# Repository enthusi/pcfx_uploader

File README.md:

# PCFX Uploader
transmitting data from PC to a NEC PC-FX via microcontroller in GPL v3 licence.

## Build
*microcontroller_code* contains the firmware in assembly for the LonganNano.\
*RP2040_device* contains information on how to build an alternate microcontroller board, and firmware (C & PIO Assembly) for this board.\
*pc_code* with the python script to upload data via UART connection.\
*pcfx_code* contains the client on NEC PC-FX side in v810 assembly (`make cd` will build an CD bin/cue image).

To build just type ```make``` in the corresponding folder, or launch the script, given that you have the following tools in your path:\
[RV32 Assembler Bronzebeard](https://github.com/theandrew168/bronzebeard)\
[v810 binutils](https://github.com/jbrandwood/v810-gcc)\
[pcfx-tools](https://github.com/jbrandwood/pcfxtools)

The RP2040 device is based on pico-sdk version 1.4.0.  To build, execute the command within 'build_xiao.sh', then 'cd build', and 'make'\
[pico-sdk](https://github.com/raspberrypi/pico-sdk)

## Summary
- the code on the PCFX side expects a magic word, start-address, execution-address and data length
- the code on the microcontroller mimics a PC-FX controller and sends all 32 keypad bits in the PC-FX specific protocol
- the code on the PC side simply connects to the microcontroller via UART
- The overall transmission speed is close to the UART limit despite a couple of extended wait loops on the PC-FX side. That could be optimized for speed if one really wanted to.

## Setup

### Longan Nano
This setup was used for initial development. The RP2040-based board will become the main supported plattform.\
The Longan Nano is hooked up to Port2 of the PC-FX via 3V-5V level shifts (though it _should_ be 5V tolerant)\
It uses 5 lines: GND, VCC, CLOCK, LATCH and DATA.\
The PC-FX pulls the LATCH line to low (0 Volts) when it wants more data to come in.
Then it sends a quick clock signal HIGH,LOW,HIGH,...\
The microcontroller senses that LATCH line, if it gets low, waits for it to get high then senses the CLOCK line and makes sure to put the proper
signal on the output DATA depending on the state of your data bit (0 or 1). Initially, I tested that in C on the raspberry PI with _some_ success.
But it became clear that it would be too instable. Then I went for a microcontroller (with only ~100 Mhz) in C. That worked but I wasn't totally happy.
Then I recoded the microcontroller in plain assembly (32bit RiscV, not too different from the PC-FX's native v810 CPU btw).
The PC connects via UART to the native UART lines of the Longan Nano.

### RP2040-based board
This operates the same as the Longan Nano, except observes the /OE line, which was found to control the direction of data on the DATA line (which
means that data can flow both *to* and *from* the PC-FX).
When this signal is high, the PC-FX sends data, so the microcontroller's output data line is tri-stated, and the signal is routed to an
alternate pin to be used for inbound data.
PIO assembly language is used for signal switching at high speeds, as this is its strength; the 'C' code merely acts as a traffic manager
for the data.
On this board, the USB port is used a virtual COM port, in order to keep the parts count to a minimum.

## Demonstration
YouTube recording of initial LonganNano variant:\

## Credits
- PC-FX code and Longan board design and code: *Martin 'enthusi' Wendt* [PriorArt](https://priorartgames.eu)
- RP2040 board design and code: *David Shadoff*

the folder *pc_code* contains the PC-FX binary `mandelbrot` from
[PC-FX Mandelbrot](https://github.com/enthusi/pcfx_fractal) which you can use to send as an example `python pysend.py mandelbrot`.\
See also: [PriorArt website](https://priorartgames.eu/2022/10/03/demo-mandelbrot-for-nec-pc-fx/)

## Research
[David Shadoff](https://github.com/dshadoff) tested the signals from '[test data line release'](https://github.com/enthusi/pcfx_uploader/releases/tag/testing_output) based on a RP2040 setup with his logic analyzer and confirms our expectation, that the data line is indeed bidirectional. Also the OE signal change flags the used direction.\

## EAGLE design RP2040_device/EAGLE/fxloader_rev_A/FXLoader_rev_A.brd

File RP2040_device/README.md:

# PCFX Uploader RP2040 Device

## Overview

This section of the repository includes PC Board designs and instructions for building a PC-FX communications device, and
also includes the firware in order to work in concert with the PC-FX and PC components elsewhere in this repository.

## PC Boards and Assembly

I designed all boards using the free version of EAGLE (2-layer, less than 100mm on both X- and Y- axes).
The gerbers are included in this repository, in case you want to get your own set made.

I have included the gerbers and relevant bom.csv and assembly.csv files to get these boards
assembled by JLCPCB, but you will still need the following parts:
- (1) Seeed Studio XIAO RP2040 microcontroller board
- (1) 6-pin right-angle through-hole pin header with 0.1" spacing.
- (7) Mill-Max Manufacturing part number 4401-0-15-80-18-27-04-0 "Receptacle with a standard tail" for creating a custom controller connector.
These are available at Digi-Key/Mouser.

You may also want to use male/female pin header sockets in case you need to remove the microcontroller board.
I recommend using short/low-profile header sockets in this case.

... These boards are solderable along the castellation, which is the recommended approach for assembly.

### Steps to assembly - Connector Board

Soldering the connector has a slightly more complicated process than the microcontroller board.  It's best not to have the pins penetrate all
the way through the board.  This is how I do it:
1. Insert the 7 Mill-Max connector pins into the PC-FX connector; you can use a pair of needle-nose pliers to assist in positioning.
2. Make sure to have one or two strands of speaker wire between the rows of pins; these will be used to extract the connector when
soldering is complete, but this wire should not be soldered to any part of the connector.
3. Position the connector board on top of the pins so that the silkscreen printing is facing up. Allow the pins to penetrate the holes slightly
but try to have them remain nearly flush with the PC board.

4. Ensure that the empty row of pins (which we will use for the right-angle pin headers) is not so close to the PC-FX; we would not want
them to be shorted by the slightly-visible metal faceplate when inserted.
5. Solder the pins in place
6. Use the wire to carefully extract the connectr assembly.

7. For the right-angle pin header, use angle clippers to remove some of the height of the pins so that they don't emerge through the
other side of the board when inserted.  The board should be 1.6mm thick; roughly 1.2mm-1.5mm of pin should be sufficient.
8. Solder the pin headers into place, with the long end facing inward; these will hold the main board in place.
9. Keep the solder on these holes as flat as possible; there is an opportunity to apply nail polish or some other NON-CONDUCTIVE
coating to ensure that they don't get shorted out by any metal hear the connector socket.

### Steps to assembly - RP2040 Board

1. Position the Seed RP2040 board on the top side carrier board (where other parts are also mounted), such that the holes are aligned
(you may wish to use a pin header or two to anchor it in place). Solder the boards together at the castellation as shown in the photo.

2. Insert the headers from the connector board through the holes on the RP2040 board.  Be careful to ensure that the pins are on the
opposite side from the parts (i.e. the pins seem to "emerge" upwards when looking at the 'top' of the board where the parts are mounted).
This connection should be tight enough that the pins can hold the board in place.

3. With the board positioned roughly midway between the rows of the connector pins, solder the header pins into place.

4. Program the microncontroller board accroudng to the steps in "Programming the Microcontroller Board" below.

## Source Code

### Compilation

This code was built to use Pico-SDK version 1.4.0, which may not be the newest version when you read this, but shouldn't have any
features which will change in futue versions (although it requires some components which were only made available in 1.4.0, so is
not backward-compatible).

pico_sdk_import.cmake is from the SDK, but is required by CMake (and thus replicated here)

This is based on the TinyUSB Host HID example, and since this often changes (required by refactoring of
the Host HID code), the initial commit baseline is the source ocde of that example.

To build the source, first ensure that you have the right version of the RaspberryPi/piso-sdk installed.
As this board targets the Seeed Studio XIAO RP2040 board, you should run the "make_xiao.sh" script (under UNIX).
Then, "cd build" and "make".

### Programming the Microcontroller Board

I have also included a release version of the program as a uf2 file in the releases/ folder.

To put the device into BOOTSEL mode, the board must be rebooted with the 'Boot' button pressed.  This can be done one of two ways:
1. Press and hold the button marked as 'B' (boot) while the USB is connected to a computer (and then release after power is applied), OR
2. Connect the USB to a computer, then press and hold the button marked as 'B' (boot), and while continuing to hold that button, press and
release the button marked as 'R' (reset).
The board will reboot in DFU mode, and will present itself as a USB drive to the host PC.

Then, just drag and drop the .uf2 file onto the USB drive which is presented.

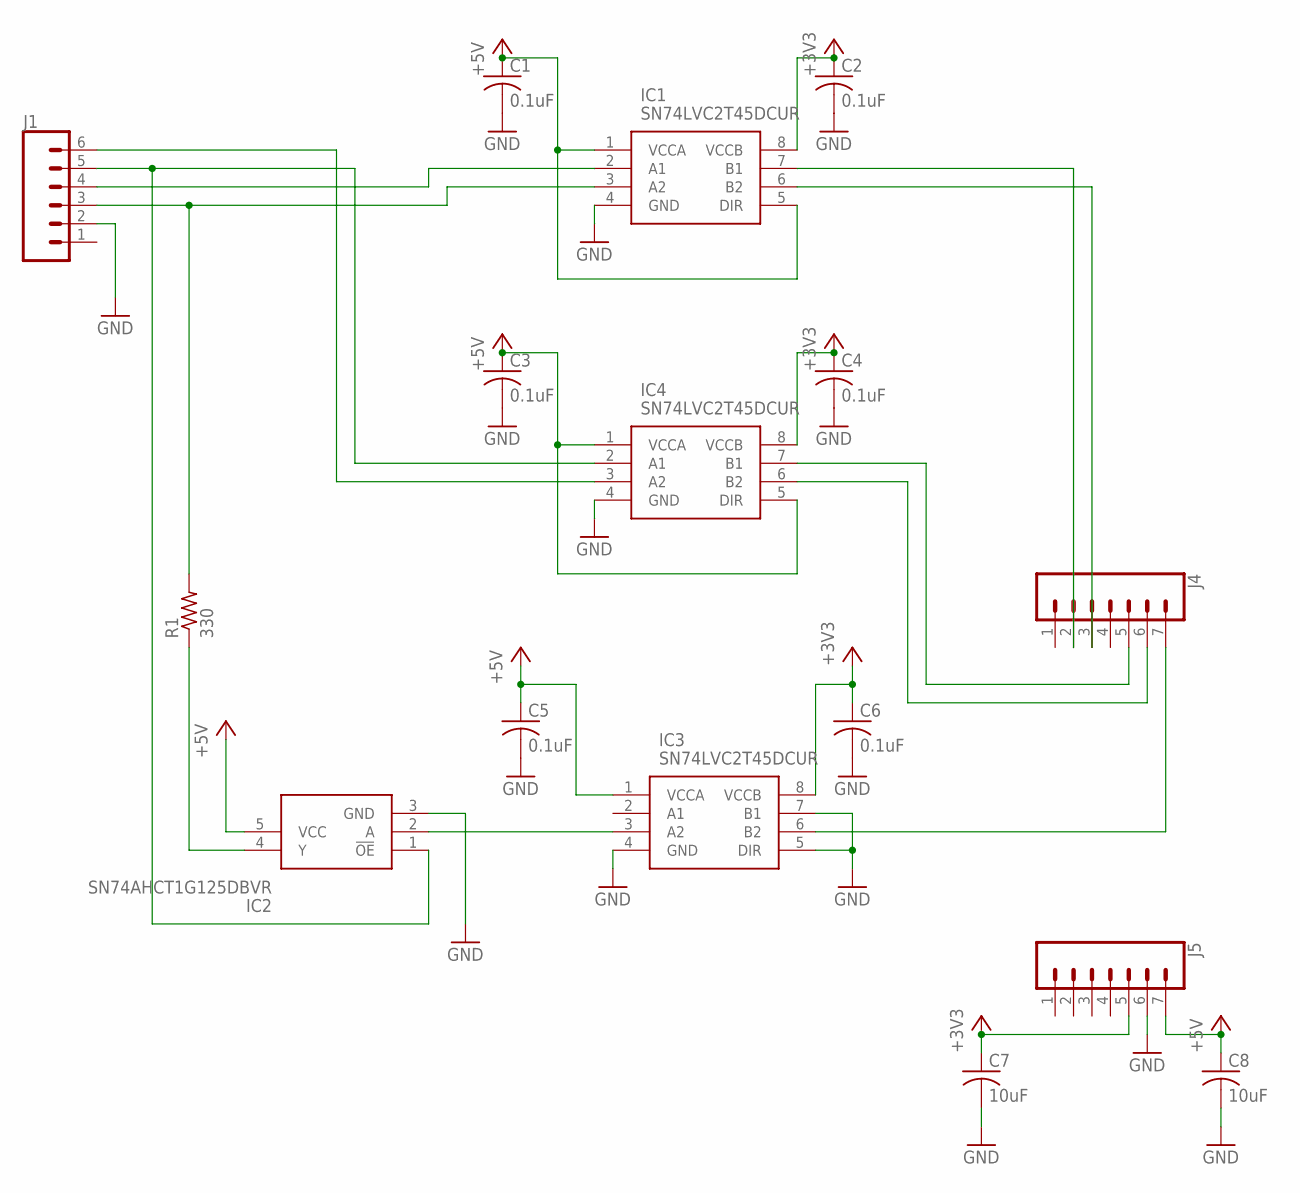
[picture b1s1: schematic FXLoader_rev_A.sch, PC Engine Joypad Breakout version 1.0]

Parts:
C1, C2, C3, C4, C5, C6: 0.1uF; C0402
C7, C8: 10uF; C0805
IC1, IC3, IC4: SN74LVC2T45DCUR; SOP50P310X90-8N
IC2: SN74AHCT1G125DBVR; SOT95P280X145-5N
J1: CONN_06NO_SILK_FEMALE_PTH; 1X06_NO_SILK
J4: CONN_071X07_LONGPADS_OFFSET_B; 1X07_LONGPADS_OFFSET_B
J5: CONN_071X07_LONGPADS_OFFSET; 1X07_LONGPADS_OFFSET
R1: 330; R0402

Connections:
+3V3: C2.1, C4.1, C6.1, C7.1, IC1.8 (VCCB), IC3.8 (VCCB), IC4.8 (VCCB), J5.5
+5V: C1.1, C3.1, C5.1, C8.1, IC1.1 (VCCA), IC1.5 (DIR), IC2.5 (VCC), IC3.1 (VCCA), IC4.1 (VCCA), IC4.5 (DIR), J5.7
CLK: IC1.2 (A1), J1.4
DATA: IC1.3 (A2), J1.3, R1.2
GND: C1.2, C2.2, C3.2, C4.2, C5.2, C6.2, C7.2, C8.2, IC1.4 (GND), IC2.3 (GND), IC3.4 (GND), IC3.5 (DIR), IC3.7 (B1), IC4.4 (GND), J1.2, J5.6
unnamed: IC2.2 (A), IC3.3 (A2)
unnamed: IC1.7 (B1), J4.2
unnamed: IC3.6 (B2), J4.7
unnamed: IC2.4 (Y), R1.1
unnamed: IC4.3 (A2), J1.6
unnamed: IC4.6 (B2), J4.6
unnamed: IC1.6 (B2), J4.3
unnamed: IC4.7 (B1), J4.5
W/R: IC2.1 (!OE), IC4.2 (A1), J1.5

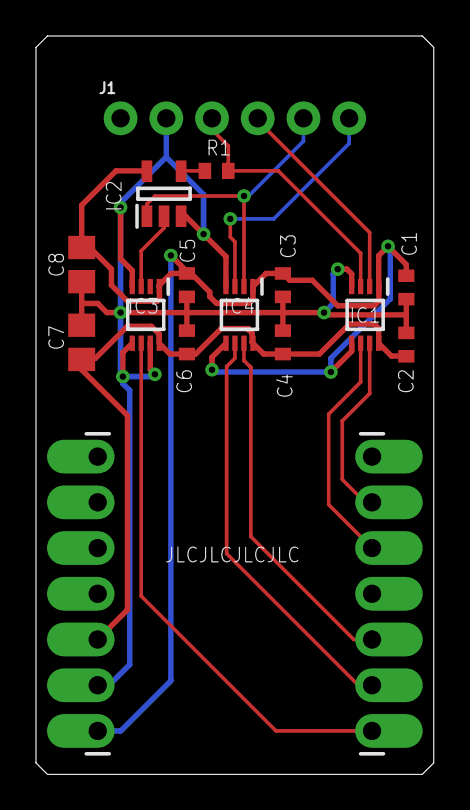
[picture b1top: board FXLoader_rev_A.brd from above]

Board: 2 copper layers, 22.1 x 41.0 mm, 16 parts (0 on the bottom side), 14 nets.

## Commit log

2022-10-06 initial push
2022-10-06 adds header and CDROM image
2022-10-06 adds headers
2022-10-10 adds a sender code for testing
2022-10-10 Add Windows COM port support. Needs to be at end of command line
2022-10-11 adds measurements by dshadoff
2022-10-19 Initial RP2040 device commit
2022-10-24 Add documentation
2022-10-24 crop photos
2022-10-24 Fix rotation
2022-10-24 adjust pictures
2022-10-28 global _start in loader/sender and cache clear up
2022-10-30 Add data fetch capability
    - New version of PC code and PCFX code to send (and save) backup RAM (getbram, getbram.py)
    -- Includes roughed-in functions for sending blocks of memory to host
    - Note: you need to press a button on the controller to send data back
    - New version for RP2040 includes:
    -- support for the large LED for signalling;
    --- startup countdown ready when LED is white.
2022-11-03 adds loader_gfx as prime target, use `make run_gfx`
2022-11-09 Add looping read commands to PC, MCU, and FX code
2022-11-13 Add Write capability, separate python into library + programs
2022-11-15 Update write routines to batch data into blocks with writefx()
2022-11-18 Add EXEC function
2022-11-18 After bootloader update is ready, these are small utilities
2022-11-19 getram2
2022-11-19 binary getram2 as well
2022-11-20 some fixes. Runs stable so far
2022-11-20 faster keypad read
2022-11-21 bug in IRQ vector clear which didnt matter but was still wrong :)
2022-11-21 relocation address labelled
2022-11-21 now sendword also relocatable via SP
2022-11-22 not tested, with words
2022-11-23 list blocks for RDBR WRBR as well
2022-11-23 changed the font
2022-11-23 removes font demo debug mode
2022-11-29 client for CD release
2022-11-30 Remove forced-deploy of loader program
    With the release of the improved loader CD image, these updates remove the vestigial requirements for deploying a test loader as an intermediate step.
    RP2040 firmware:
    - Remove expectation that a program will be loaded before read/write commands
    PC Python code:
    - Remove "<program|nodeploy>" argument from putram/getram,
    - Remove deploy_program function from fxlib
2023-05-21 Microcontroller code: Clean receive queue before and after transfer; clean up old releases
2023-05-22 Update comments
2023-05-22 update comment
2023-05-22 Fix scan completion detect and word count on round-number transfers
2023-05-27 Add additional "sacrificial word" in outbound data stream
2023-05-27 Add longer pause on PC-FX side between blocks
2023-05-28 Limit the amount of buffering required on the RP2040 by adding block ACK to the protocol
2023-06-03 Improve transient suppression on edge-trigger
2023-06-03 Some "ReadPad" scans failed due to hardware; various compensating tactics

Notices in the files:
RP2040_device/EAGLE/fxloader_rev_A/FXLoader_rev_A.brd:
(C)2022 David Shadoff
parts and their libraries:
SparkFun-Connectors: Licensing: Creative Commons ShareAlike 4.0 International - https://creativecommons.org/licenses/by-sa/4.0
